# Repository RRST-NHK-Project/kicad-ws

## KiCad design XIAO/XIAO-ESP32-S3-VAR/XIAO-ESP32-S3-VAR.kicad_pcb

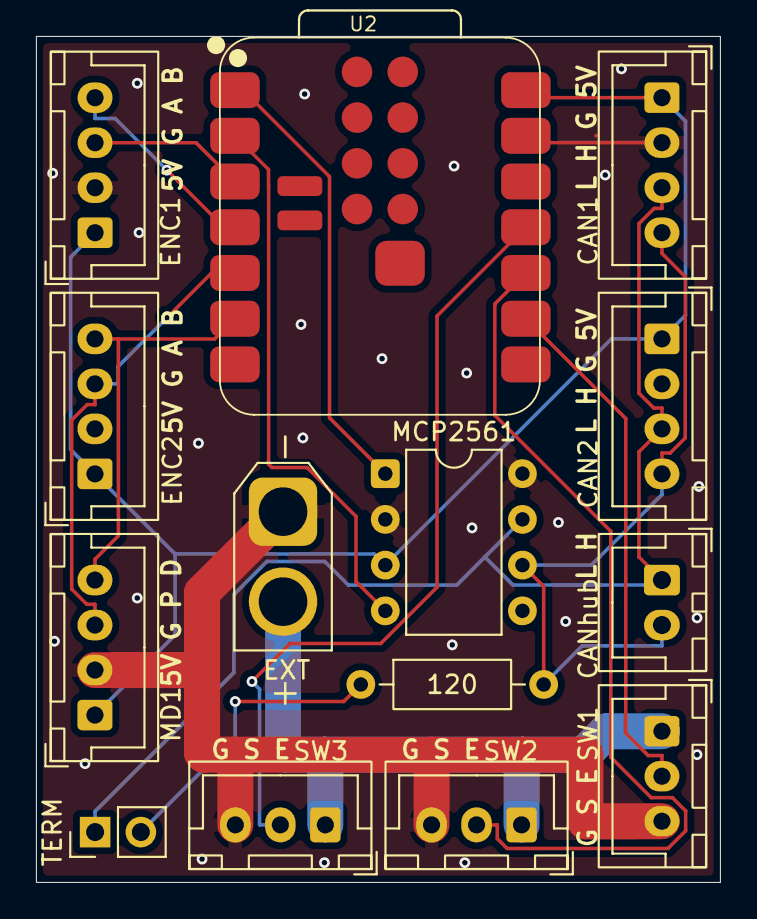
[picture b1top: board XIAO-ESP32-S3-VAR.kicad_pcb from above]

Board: 2 copper layers, 38.0 x 47.0 mm, 14 parts (0 on the bottom side), 15 nets.

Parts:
120: 120; R_Axial_DIN0207_L6.3mm_D2.5mm_P10.16mm_Horizontal
CAN1: CAN1; JST_XH_B4B-XH-A_1x04_P2.50mm_Vertical
CAN2: CAN2; JST_XH_B4B-XH-A_1x04_P2.50mm_Vertical
CANhub: CANhub; JST_XH_B2B-XH-A_1x02_P2.50mm_Vertical
ENC1: ENC1; JST_XH_B4B-XH-A_1x04_P2.50mm_Vertical
ENC2: ENC2; JST_XH_B4B-XH-A_1x04_P2.50mm_Vertical
EXT: Conn_01x02_Pin; AMASS_XT30U-M_1x02_P5.0mm_Vertical
MCP2561: DIP-8_W7.62mm
MD1: MD1; JST_XH_B4B-XH-A_1x04_P2.50mm_Vertical
SW1: SW1; JST_XH_B3B-XH-A_1x03_P2.50mm_Vertical
SW2: SW2; JST_XH_B3B-XH-A_1x03_P2.50mm_Vertical
SW3: SW3; JST_XH_B3B-XH-A_1x03_P2.50mm_Vertical
TERM: R120; PinHeader_1x02_P2.54mm_Vertical
U2: XIAO-ESP32-S3-SMD

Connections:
5V0: CAN1.1, CAN2.1, ENC1.1, ENC2.1, MCP2561.3 (Vdd), MD1.1, U2.14 (VBUS)
CANH: CAN1.3, CAN2.3, CANhub.1, MCP2561.7 (CANH), TERM.1
CANL: 120.2, CAN1.4, CAN2.4, CANhub.2, MCP2561.6 (CANL)
CAN_RX: MCP2561.4 (Rxd), U2.2 (GPIO2_A1_D1)
CAN_TX: MCP2561.1 (Txd), U2.1 (GPIO1_A0_D0)
ENC1_A/MD2P: ENC1.3, U2.3 (GPIO3_A2_D2)
ENC1_B/MD2D: ENC1.4, U2.4 (GPIO4_A3_D3)
EXT_POWER: EXT.2, SW1.1, SW2.1, SW3.1
GND: CAN1.2, CAN2.2, ENC1.2, ENC2.2, EXT.1, MCP2561.2 (Vss), MCP2561.8 (STBY), MD1.2, SW1.3, SW2.3, SW3.3, U2.13 (GND)
GPIO5: ENC2.3, MD1.3, U2.5 (GPIO5_A4_D4_SDA)
GPIO6: ENC2.4, MD1.4, U2.6 (GPIO6_A5_D5_SCL)
GPIO7: SW1.2, U2.9 (GPIO7_A8_D8_SCK)
GPIO8: SW2.2, U2.10 (GPIO8_A9_D9_MISO)
GPIO9: SW3.2, U2.11 (GPIO9_A10_D10_MOSI)
unnamed: 120.1, TERM.2

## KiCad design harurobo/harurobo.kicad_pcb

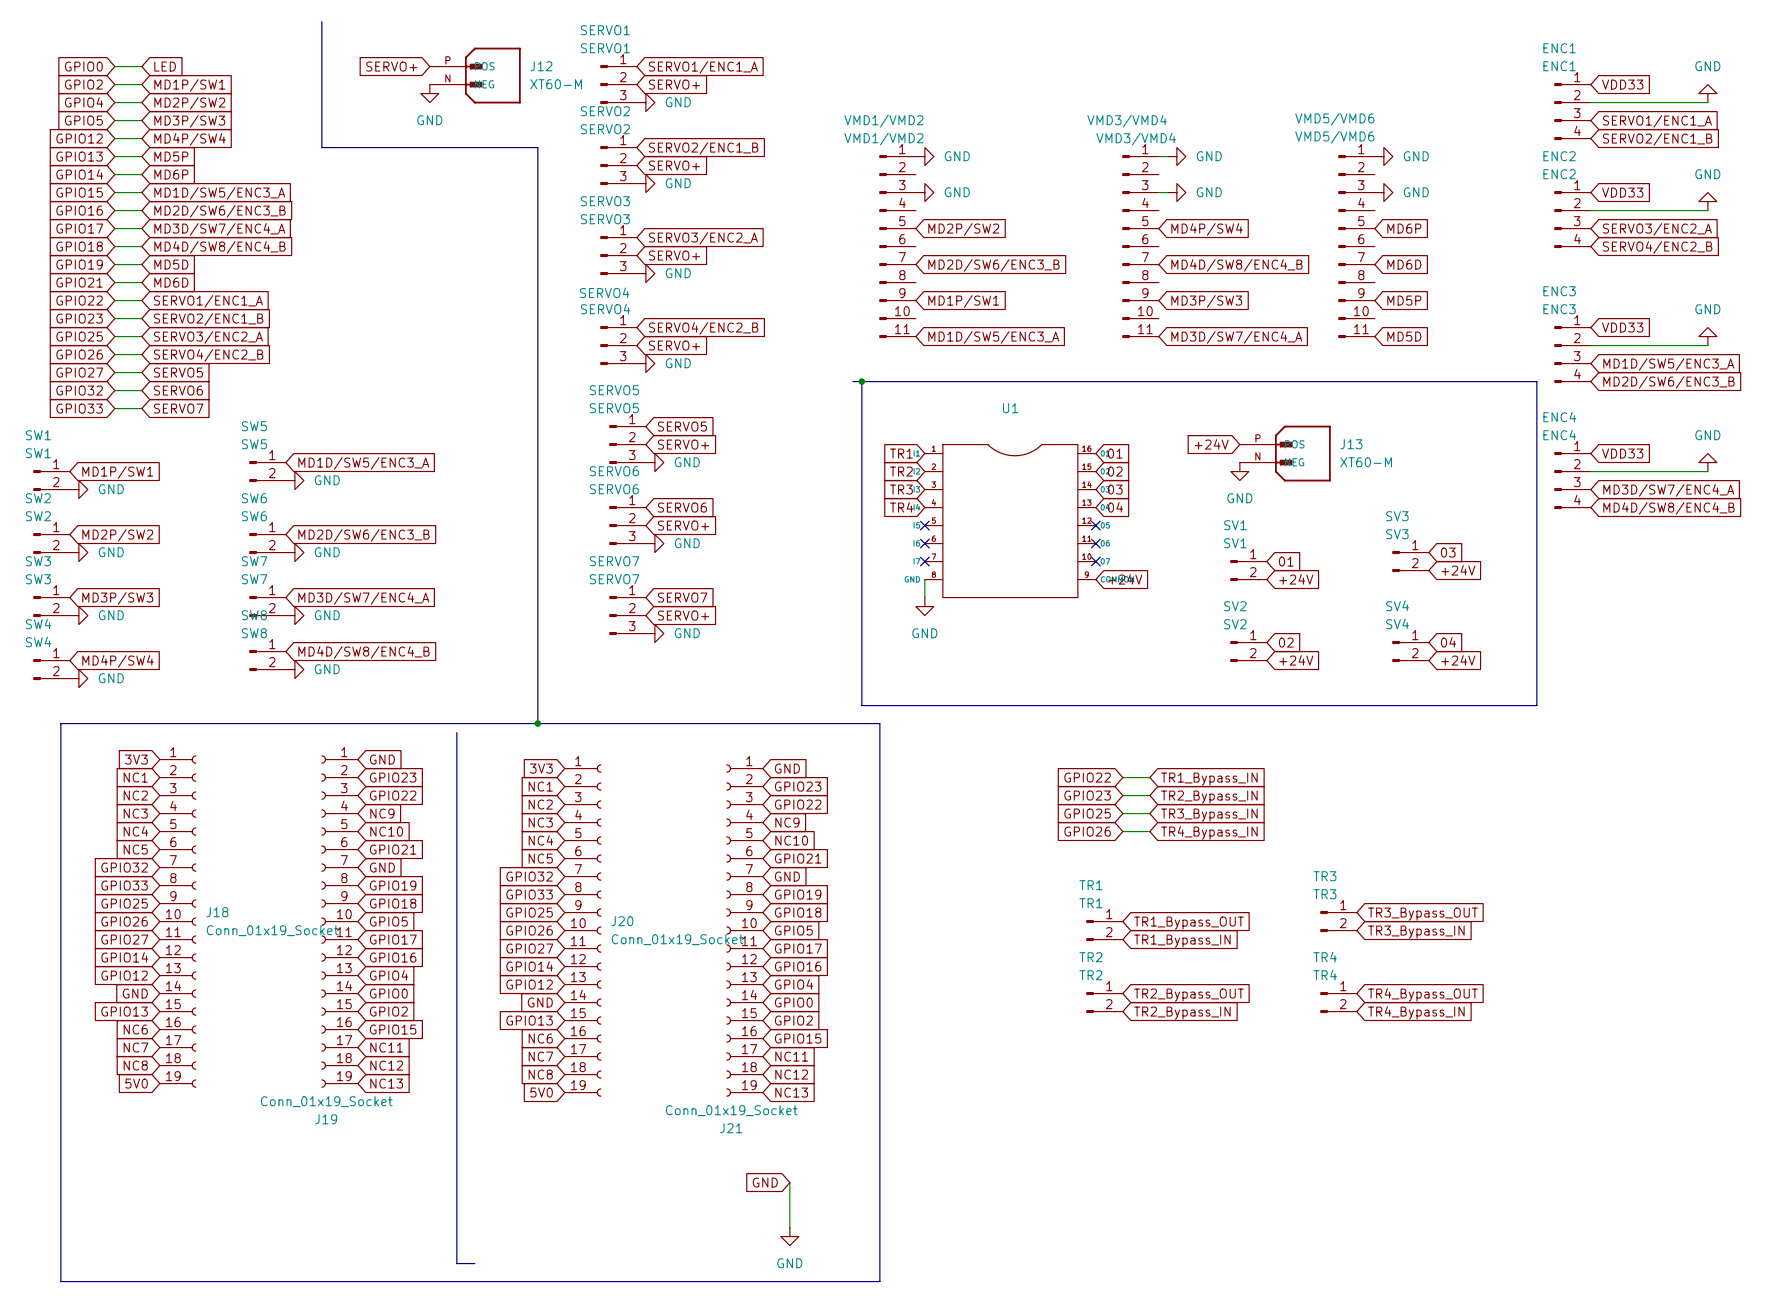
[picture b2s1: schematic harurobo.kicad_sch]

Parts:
ENC1: ENC1; JST_XH_B4B-XH-A_1x04_P2.50mm_Vertical
ENC2: ENC2; JST_XH_B4B-XH-A_1x04_P2.50mm_Vertical
ENC3: ENC3; JST_XH_B4B-XH-A_1x04_P2.50mm_Vertical
ENC4: ENC4; JST_XH_B4B-XH-A_1x04_P2.50mm_Vertical
J12, J13: XT60-M; AMASS_XT60-M; PARTREV V1.2
J18, J19, J20, J21: Conn_01x19_Socket; PinSocket_1x19_P2.54mm_Vertical
SERVO1: SERVO1; JST_XH_B3B-XH-A_1x03_P2.50mm_Vertical
SERVO2: SERVO2; JST_XH_B3B-XH-A_1x03_P2.50mm_Vertical
SERVO3: SERVO3; JST_XH_B3B-XH-A_1x03_P2.50mm_Vertical
SERVO4: SERVO4; JST_XH_B3B-XH-A_1x03_P2.50mm_Vertical
SERVO5: SERVO5; JST_XH_B3B-XH-A_1x03_P2.50mm_Vertical
SERVO6: SERVO6; JST_XH_B3B-XH-A_1x03_P2.50mm_Vertical
SERVO7: SERVO7; JST_XH_B3B-XH-A_1x03_P2.50mm_Vertical
SV1: SV1; JST_XH_B2B-XH-A_1x02_P2.50mm_Vertical
SV2: SV2; JST_XH_B2B-XH-A_1x02_P2.50mm_Vertical
SV3: SV3; JST_XH_B2B-XH-A_1x02_P2.50mm_Vertical
SV4: SV4; JST_XH_B2B-XH-A_1x02_P2.50mm_Vertical
SW1: SW1; JST_XH_B2B-XH-A_1x02_P2.50mm_Vertical
SW2: SW2; JST_XH_B2B-XH-A_1x02_P2.50mm_Vertical
SW3: SW3; JST_XH_B2B-XH-A_1x02_P2.50mm_Vertical
SW4: SW4; JST_XH_B2B-XH-A_1x02_P2.50mm_Vertical
SW5: SW5; JST_XH_B2B-XH-A_1x02_P2.50mm_Vertical
SW6: SW6; JST_XH_B2B-XH-A_1x02_P2.50mm_Vertical
SW7: SW7; JST_XH_B2B-XH-A_1x02_P2.50mm_Vertical
SW8: SW8; JST_XH_B2B-XH-A_1x02_P2.50mm_Vertical
TR1: TR1; PinHeader_1x02_P2.54mm_Vertical
TR2: TR2; PinHeader_1x02_P2.54mm_Vertical
TR3: TR3; PinHeader_1x02_P2.54mm_Vertical
TR4: TR4; PinHeader_1x02_P2.54mm_Vertical
U1: DIP-16_W7.62mm
VMD1/VMD2: VMD1/VMD2; PinHeader_1x11_P2.54mm_Vertical
VMD3/VMD4: VMD3/VMD4; PinHeader_1x11_P2.54mm_Vertical
VMD5/VMD6: VMD5/VMD6; PinHeader_1x11_P2.54mm_Vertical

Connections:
01: SV1.1
02: SV2.1
03: SV3.1
3V3: J18.1, J20.1
04: SV4.1
5V0: J18.19, J20.19
+24V: J13.P (POS), SV1.2, SV2.2, SV3.2, SV4.2
GND: ENC1.2, ENC2.2, ENC3.2, ENC4.2, J12.N (NEG), J13.N (NEG), J18.14, J19.1, J19.7, J20.14, J21.1, J21.7, SERVO1.3, SERVO2.3, SERVO3.3, SERVO4.3, SERVO5.3, SERVO6.3, SERVO7.3, SW1.2, SW2.2, SW3.2, SW4.2, SW5.2, SW6.2, SW7.2, SW8.2, VMD1/VMD2.1, VMD1/VMD2.3, VMD3/VMD4.1, VMD3/VMD4.3, VMD5/VMD6.1, VMD5/VMD6.3
GPIO0: J19.14, J21.14
GPIO2: J19.15, J21.15, SW1.1, VMD1/VMD2.9
GPIO4: J19.13, J21.13, SW2.1, VMD1/VMD2.5
GPIO5: J19.10, J21.10, SW3.1, VMD3/VMD4.9
GPIO12: J18.13, J20.13, SW4.1, VMD3/VMD4.5
GPIO13: J18.15, J20.15, VMD5/VMD6.9
GPIO14: J18.12, J20.12, VMD5/VMD6.5
GPIO15: ENC3.3, J19.16, J21.16, SW5.1, VMD1/VMD2.11
GPIO16: ENC3.4, J19.12, J21.12, SW6.1, VMD1/VMD2.7
GPIO17: ENC4.3, J19.11, J21.11, SW7.1, VMD3/VMD4.11
GPIO18: ENC4.4, J19.9, J21.9, SW8.1, VMD3/VMD4.7
GPIO19: J19.8, J21.8, VMD5/VMD6.11
GPIO21: J19.6, J21.6, VMD5/VMD6.7
GPIO22: ENC1.3, J19.3, J21.3, SERVO1.1, TR1.2
GPIO23: ENC1.4, J19.2, J21.2, SERVO2.1, TR2.2
GPIO25: ENC2.3, J18.9, J20.9, SERVO3.1, TR3.2
GPIO26: ENC2.4, J18.10, J20.10, SERVO4.1, TR4.2
GPIO27: J18.11, J20.11, SERVO5.1
GPIO32: J18.7, J20.7, SERVO6.1
GPIO33: J18.8, J20.8, SERVO7.1
NC1: J18.2, J20.2
NC2: J18.3, J20.3
NC3: J18.4, J20.4
NC4: J18.5, J20.5
NC5: J18.6, J20.6
NC6: J18.16, J20.16
NC7: J18.17, J20.17
NC8: J18.18, J20.18
NC9: J19.4, J21.4
NC10: J19.5, J21.5
NC11: J19.17, J21.17
NC12: J19.18, J21.18
NC13: J19.19, J21.19
SERVO+: J12.P (POS), SERVO1.2, SERVO2.2, SERVO3.2, SERVO4.2, SERVO5.2, SERVO6.2, SERVO7.2
TR1_Bypass_OUT: TR1.1
TR2_Bypass_OUT: TR2.1
TR3_Bypass_OUT: TR3.1
TR4_Bypass_OUT: TR4.1
VDD33: ENC1.1, ENC2.1, ENC3.1, ENC4.1

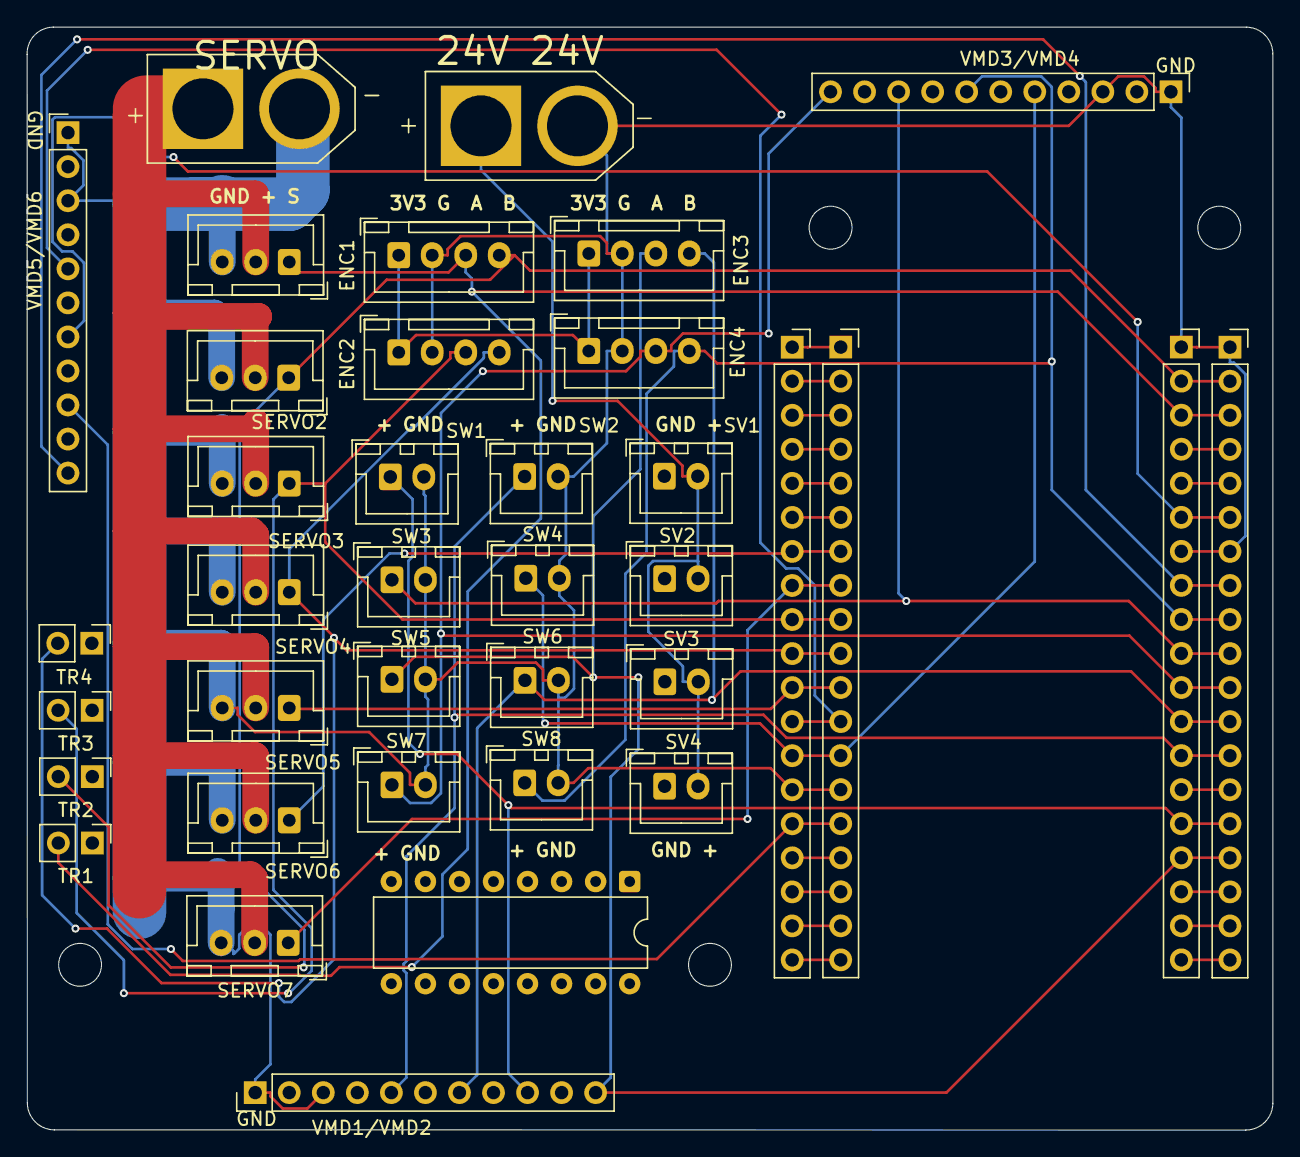
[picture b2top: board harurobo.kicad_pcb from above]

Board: 2 copper layers, 93.0 x 82.3 mm, 41 parts (0 on the bottom side), 39 nets.

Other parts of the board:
REF1**, REF2**, REF3**, REF4**: MountingHole_3.2mm_M3

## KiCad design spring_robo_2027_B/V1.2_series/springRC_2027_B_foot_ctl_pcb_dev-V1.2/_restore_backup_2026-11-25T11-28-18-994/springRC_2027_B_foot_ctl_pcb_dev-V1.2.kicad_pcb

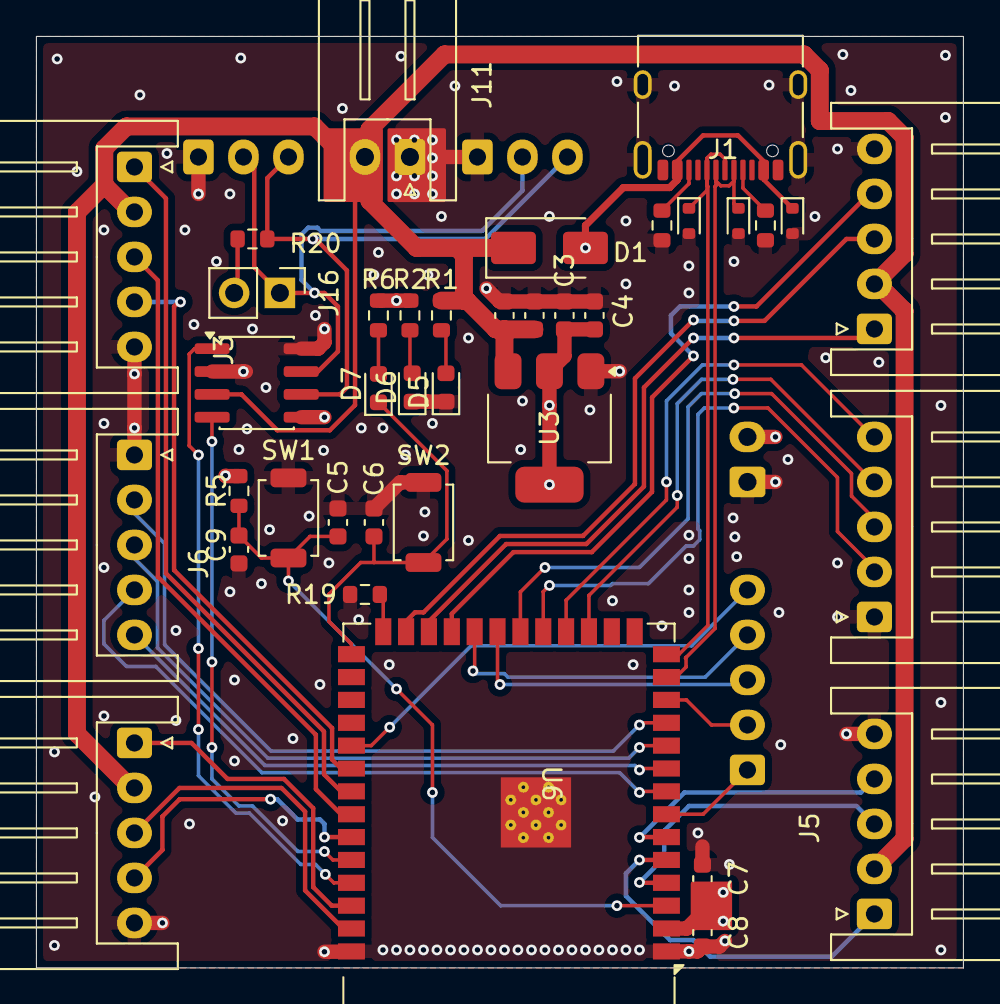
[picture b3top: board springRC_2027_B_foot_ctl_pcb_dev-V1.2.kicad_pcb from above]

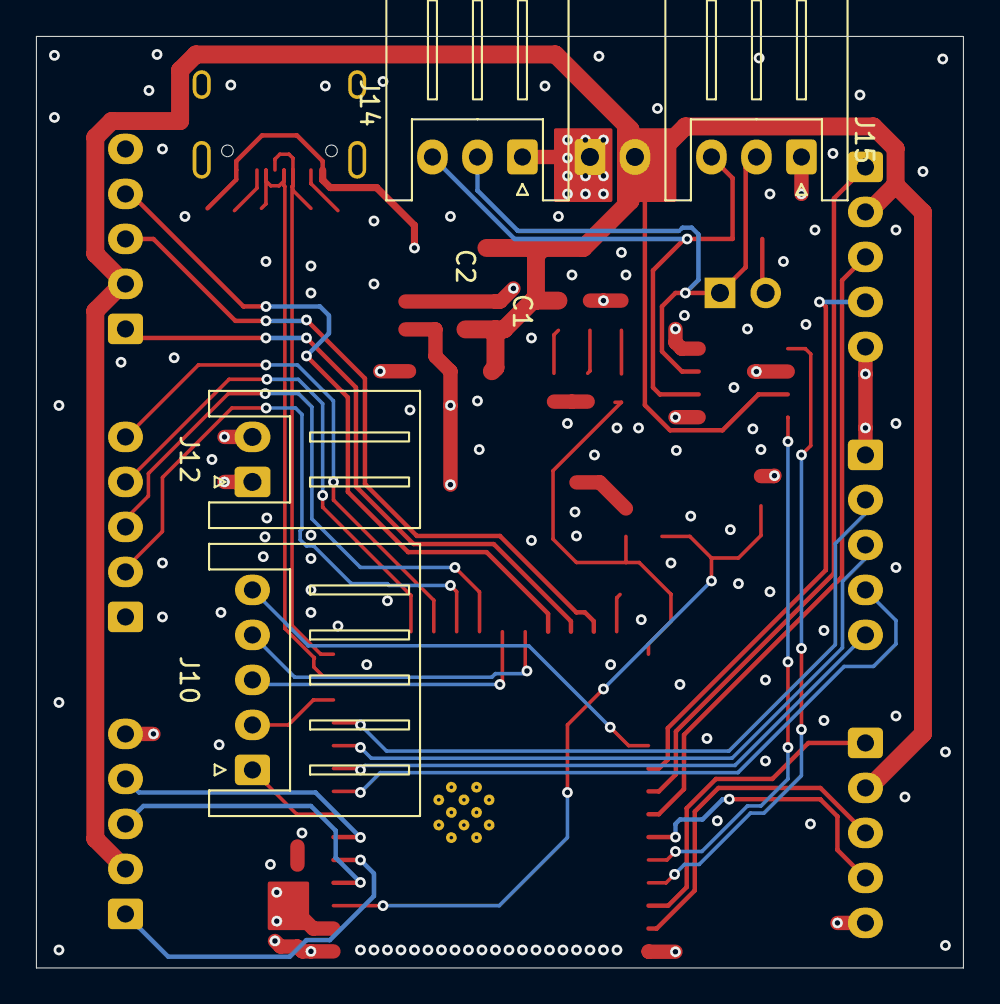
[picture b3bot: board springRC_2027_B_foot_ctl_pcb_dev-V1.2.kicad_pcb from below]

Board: 4 copper layers, 51.5 x 51.8 mm, 42 parts (4 on the bottom side), 44 nets.

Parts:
C1, C3, C7: 10uF; C_0603_1608Metric
C2, C4, C5, C6, C8: 100nF; C_0603_1608Metric
C9: 1uF; C_0603_1608Metric
D1: SS14; D_SMA
D2, D3, D4: LESD5D5.0CT1G; D_SOD-523
D5, D6, D7: LED; LED_0603_1608Metric
J1: USB_C_Receptacle_USB2.0_16P; USB_C_Receptacle_XKB_U262-16XN-4BVC11
J2, J3, J4, J5, J6, J7, J10: Conn_01x05_Socket; JST_XH_S5B-XH-A_1x05_P2.50mm_Horizontal
J11, J12: Conn_01x02_Socket; JST_XH_S2B-XH-A_1x02_P2.50mm_Horizontal
J14, J15: Conn_01x03_Socket; JST_XH_S3B-XH-A_1x03_P2.50mm_Horizontal
J16: Conn_01x02_Pin; PinHeader_1x02_P2.54mm_Vertical
R1, R2, R3, R4: 5.1k; R_0603_1608Metric
R5: 10k; R_0603_1608Metric
R6: 330; R_0603_1608Metric
R19: 1k; R_0603_1608Metric
R20: 120; R_0603_1608Metric
SW1, SW2: SW_Push; SW_SPST_TS-1088-xR020
U1: MCP2562FD-E-SN; SOIC-8_3.9x4.9mm_P1.27mm
U3: LD1117S33TR_SOT223; SOT-223-3_TabPin2
U6: ESP32-S3-WROOM-1-N16R8; ESP32-S3-WROOM-1

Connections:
3V3: C3.2, C4.2, C7.1, C8.1, J12.2, R2.1, R5.1, R6.2, U1.5 (Vio), U3.2 (VO), U6.2 (3V3)
+5V: C1.1, C2.1, D1.1 (K), J2.2, J3.2, J4.2, J5.2, J11.2, R1.1, U1.3 (VDD), U3.3 (VI)
CAN_H: J14.2, J15.2, J16.1, U1.7 (CANH)
CAN_L: J14.3, J15.3, R20.1, U1.6 (CANL)
CAN_RX: U1.4 (RXD), U6.36 (RXD0)
CAN_TX: U1.1 (TXD), U6.37 (TXD0)
DN: D3.1, J1.A7 (D-), J1.B7 (D-), U6.13 (USB_D-)
DP: D4.1, J1.A6 (D+), J1.B6 (D+), U6.14 (USB_D+)
EN: C5.1, C9.1, R5.2, SW1.2, U6.3 (EN)
ENC1_A: J2.3, U6.39 (IO1)
ENC1_B: J2.1, U6.38 (IO2)
ENC1_X: J2.4, U6.35 (IO42)
ENC2_A: J3.3, U6.34 (IO41)
ENC2_B: J3.1, U6.33 (IO40)
ENC2_X: J3.4, U6.32 (IO39)
ENC3_A: J4.3, U6.25 (IO48)
ENC3_B: J4.1, U6.24 (IO47)
ENC3_X: J4.4, U6.23 (IO21)
ENC4_A: J5.3, U6.4 (IO4)
ENC4_B: J5.1, U6.5 (IO5)
ENC4_X: J5.4, U6.6 (IO6)
GND: C1.2, C2.2, C3.1, C4.1, C5.2, C6.2, C7.2, C8.2, C9.2, D2.2, D3.2, D4.2, D5.1 (K), D6.1 (K), J1.A1 (GND), J1.A12 (GND), J1.B1 (GND), J1.B12 (GND), J1.S1 (SHIELD), J2.5, J3.5, J4.5, J5.5, J6.1, J7.1, J11.1, J12.1, J14.1, J15.1, R3.2, R4.2, R19.2, SW1.1, SW2.1, U1.2 (VSS), U1.8 (STBY), U3.1 (GND), U6.1 (GND), U6.40 (GND), U6.41 (GND)
IO0: C6.1, D7.1 (K), SW2.2, U6.27 (IO0)
IO7: J10.1, U6.7 (IO7)
IO8: J10.2, U6.12 (IO8)
IO9: J7.4, U6.17 (IO9)
IO10: J7.5, U6.18 (IO10)
IO11: J7.2, U6.19 (IO11)
IO12: J7.3, U6.20 (IO12)
IO13: J10.3, U6.21 (IO13)
IO14: J10.4, U6.22 (IO14)
IO15: J6.4, U6.8 (IO15)
IO16: J6.5, U6.9 (IO16)
IO17: J6.3, U6.10 (IO17)
IO18: J6.2, U6.11 (IO18)
IO38: J10.5, U6.31 (IO38)
IO45: R19.1, U6.26 (IO45)
unnamed: D5.2 (A), R1.2
unnamed: D6.2 (A), R2.2
unnamed: D7.2 (A), R6.1
unnamed: J1.A5 (CC1), R4.1
unnamed: J1.B5 (CC2), R3.1
unnamed: J16.2, R20.2
VBUS: D1.2 (A), D2.1, J1.A4 (VBUS), J1.A9 (VBUS), J1.B4 (VBUS), J1.B9 (VBUS)

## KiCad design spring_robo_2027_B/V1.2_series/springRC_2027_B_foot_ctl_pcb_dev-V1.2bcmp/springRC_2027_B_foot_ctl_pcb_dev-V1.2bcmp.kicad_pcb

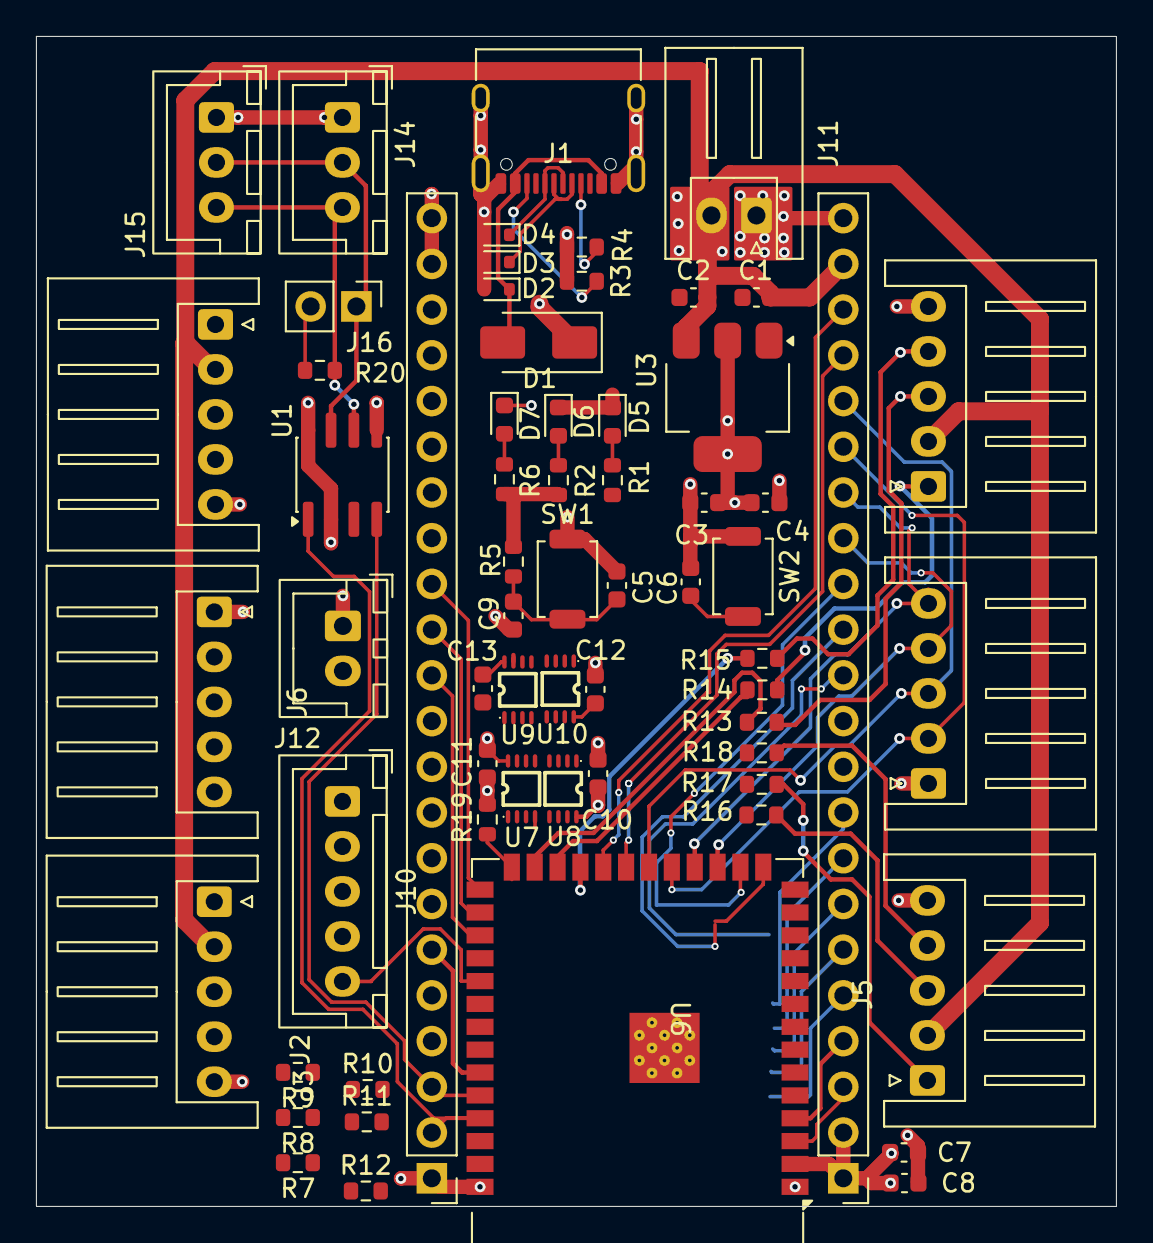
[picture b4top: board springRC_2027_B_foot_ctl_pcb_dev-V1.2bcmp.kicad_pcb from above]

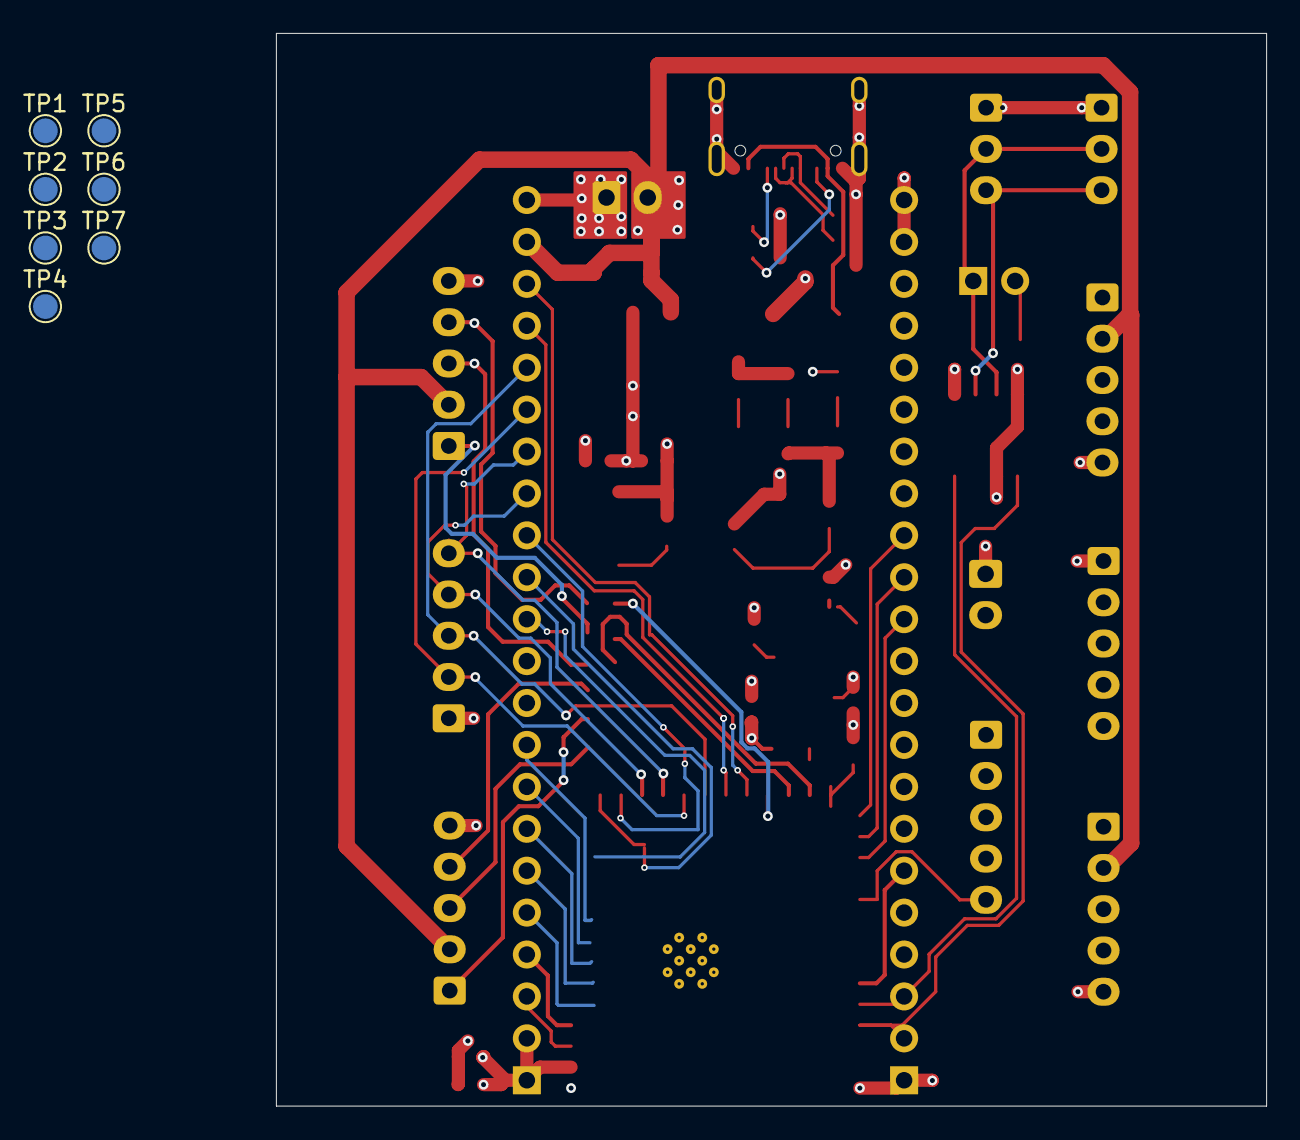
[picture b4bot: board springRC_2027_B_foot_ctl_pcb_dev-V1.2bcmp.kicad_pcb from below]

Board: 4 copper layers, 60.0 x 65.0 mm, 71 parts (7 on the bottom side), 61 nets.

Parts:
C1, C3, C7: 10uF; C_0603_1608Metric
C2, C4, C5, C6, C8, C10, C11, C12, C13: 100nF; C_0603_1608Metric
C9: 1uF; C_0603_1608Metric
D1: SS14; D_SMA
D2, D3, D4: LESD5D5.0CT1G; D_SOD-523
D5, D6, D7: LED; LED_0603_1608Metric
J1: USB_C_Receptacle_USB2.0_16P; USB_C_Receptacle_XKB_U262-16XN-4BVC11
J2, J3, J4, J5, J6, J7: Conn_01x05_Socket; JST_XH_S5B-XH-A_1x05_P2.50mm_Horizontal
J8, J9: Conn_01x22_Pin; PinHeader_1x22_P2.54mm_Vertical
J10: Conn_01x05_Socket; JST_XH_B5B-XH-A_1x05_P2.50mm_Vertical
J11: Conn_01x02_Socket; JST_XH_S2B-XH-A_1x02_P2.50mm_Horizontal
J12: Conn_01x02_Socket; JST_XH_B2B-XH-A_1x02_P2.50mm_Vertical
J14, J15: Conn_01x03_Socket; JST_XH_B3B-XH-A_1x03_P2.50mm_Vertical
J16: Conn_01x02_Pin; PinHeader_1x02_P2.54mm_Vertical
R1, R2, R3, R4: 5.1k; R_0603_1608Metric
R5: 10k; R_0603_1608Metric
R6: 330; R_0603_1608Metric
R7, R8, R9, R10, R11, R12, R13, R14, R15, R16, R17, R18: 0R; R_0603_1608Metric
R19: 1k; R_0603_1608Metric
R20: 120; R_0603_1608Metric
SW1, SW2: SW_Push; SW_SPST_TS-1088-xR020
TP1: VBUS; TestPoint_Pad_D1.5mm
TP2: CAN_H; TestPoint_Pad_D1.5mm
TP3: CAN_L; TestPoint_Pad_D1.5mm
TP4, TP7: GND; TestPoint_Pad_D1.5mm
TP5: DP; TestPoint_Pad_D1.5mm
TP6: DN; TestPoint_Pad_D1.5mm
U1: MCP2562FD-E-SN; SOIC-8_3.9x4.9mm_P1.27mm
U3: LD1117S33TR_SOT223; SOT-223-3_TabPin2
U6: ESP32-S3-WROOM-1-N16R8; ESP32-S3-WROOM-1
U7, U8, U9, U10: SN74LVC3G17DCUR; VSSOP-8_L2.1-W2.4-P0.50-LS3.2-BR

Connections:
3V3: C3.2, C4.2, C7.1, C8.1, C10.1, C11.1, C12.1, C13.1, J8.1, J8.2, J12.2, R2.1, R5.1, R6.2, U1.5 (Vio), U3.2 (VO), U6.2 (3V3), U7.8 (VCC), U8.8 (VCC), U9.8 (VCC), U10.8 (VCC)
+5V: C1.1, C2.1, D1.1 (K), J2.2, J3.2, J4.2, J5.2, J8.21, J11.2, R1.1, U1.3 (VDD), U3.3 (VI)
CAN_H: J14.2, J15.2, J16.1, TP2.1 (1_1), U1.7 (CANH)
CAN_L: J14.3, J15.3, R20.1, TP3.1 (1_1), U1.6 (CANL)
CAN_RX: J9.3, U1.4 (RXD), U6.36 (RXD0)
CAN_TX: J9.2, U1.1 (TXD), U6.37 (TXD0)
DN: D3.1, J1.A7 (D-), J1.B7 (D-), J9.20, TP6.1 (1_1), U6.13 (USB_D-)
DP: D4.1, J1.A6 (D+), J1.B6 (D+), J9.19, TP5.1 (1_1), U6.14 (USB_D+)
EN: C5.1, C9.1, J8.3, R5.2, SW1.2, U6.3 (EN)
ENC1_A: J2.3, R7.1, U7.1 (1A)
ENC1_A_BUF: J9.4, R7.2, U6.39 (IO1), U7.7 (1Y)
ENC1_B: J2.1, R8.1, U7.3 (2A)
ENC1_B_BUF: J9.5, R8.2, U6.38 (IO2), U7.5 (2Y)
ENC1_X: J2.4, R9.1, U7.6 (3A)
ENC1_X_BUF: J9.6, R9.2, U6.35 (IO42), U7.2 (3Y)
ENC2_A: J3.3, R10.1, U8.1 (1A)
ENC2_A_BUF: J9.7, R10.2, U6.34 (IO41), U8.7 (1Y)
ENC2_B: J3.1, R11.1, U8.3 (2A)
ENC2_B_BUF: J9.8, R11.2, U6.33 (IO40), U8.5 (2Y)
ENC2_X: J3.4, R12.1, U8.6 (3A)
ENC2_X_BUF: J9.9, R12.2, U6.32 (IO39), U8.2 (3Y)
ENC3_A: J4.3, R13.1, U9.1 (1A)
ENC3_A_BUF: J9.16, R13.2, U6.25 (IO48), U9.7 (1Y)
ENC3_B: J4.1, R14.1, U9.3 (2A)
ENC3_B_BUF: J9.17, R14.2, U6.24 (IO47), U9.5 (2Y)
ENC3_X: J4.4, R15.1, U9.6 (3A)
ENC3_X_BUF: J9.18, R15.2, U6.23 (IO21), U9.2 (3Y)
ENC4_A: J5.3, R16.1, U10.1 (1A)
ENC4_A_BUF: J8.4, R16.2, U6.4 (IO4), U10.7 (1Y)
ENC4_B: J5.1, R17.1, U10.3 (2A)
ENC4_B_BUF: J8.5, R17.2, U6.5 (IO5), U10.5 (2Y)
ENC4_X: J5.4, R18.1, U10.6 (3A)
ENC4_X_BUF: J8.6, R18.2, U6.6 (IO6), U10.2 (3Y)
GND: C1.2, C2.2, C3.1, C4.1, C5.2, C6.2, C7.2, C8.2, C9.2, C10.2, C11.2, C12.2, C13.2, D2.2, D3.2, D4.2, D5.1 (K), D6.1 (K), J1.A1 (GND), J1.A12 (GND), J1.B1 (GND), J1.B12 (GND), J1.S1 (SHIELD), J2.5, J3.5, J4.5, J5.5, J6.1, J7.1, J8.22, J9.1, J9.21, J9.22, J11.1, J12.1, J14.1, J15.1, R3.2, R4.2, R19.2, SW1.1, SW2.1, TP4.1 (1_1), TP7.1 (1_1), U1.2 (VSS), U1.8 (STBY), U3.1 (GND), U6.1 (GND), U6.40 (GND), U6.41 (GND), U7.4 (GND), U8.4 (GND), U9.4 (GND), U10.4 (GND)
IO0: C6.1, D7.1 (K), J9.14, SW2.2, U6.27 (IO0)
IO3: J8.13, U6.15 (IO3)
IO7: J8.7, J10.1, U6.7 (IO7)
IO8: J8.12, J10.2, U6.12 (IO8)
IO9: J7.4, J8.15, U6.17 (IO9)
IO10: J7.5, J8.16, U6.18 (IO10)
IO11: J7.2, J8.17, U6.19 (IO11)
IO12: J7.3, J8.18, U6.20 (IO12)
IO13: J8.19, J10.3, U6.21 (IO13)
IO14: J8.20, J10.4, U6.22 (IO14)
IO15: J6.4, J8.8, U6.8 (IO15)
IO16: J6.5, J8.9, U6.9 (IO16)
IO17: J6.3, J8.10, U6.10 (IO17)
IO18: J6.2, J8.11, U6.11 (IO18)
IO35: J9.13, U6.28 (IO35)
IO36: J9.12, U6.29 (IO36)
IO37: J9.11, U6.30 (IO37)
IO38: J9.10, J10.5, U6.31 (IO38)
IO45: J9.15, R19.1, U6.26 (IO45)
IO46: J8.14, U6.16 (IO46)
unnamed: D5.2 (A), R1.2
unnamed: D6.2 (A), R2.2
unnamed: D7.2 (A), R6.1
unnamed: J1.A5 (CC1), R4.1
unnamed: J1.B5 (CC2), R3.1
unnamed: J16.2, R20.2
VBUS: D1.2 (A), D2.1, J1.A4 (VBUS), J1.A9 (VBUS), J1.B4 (VBUS), J1.B9 (VBUS), TP1.1 (1_1)

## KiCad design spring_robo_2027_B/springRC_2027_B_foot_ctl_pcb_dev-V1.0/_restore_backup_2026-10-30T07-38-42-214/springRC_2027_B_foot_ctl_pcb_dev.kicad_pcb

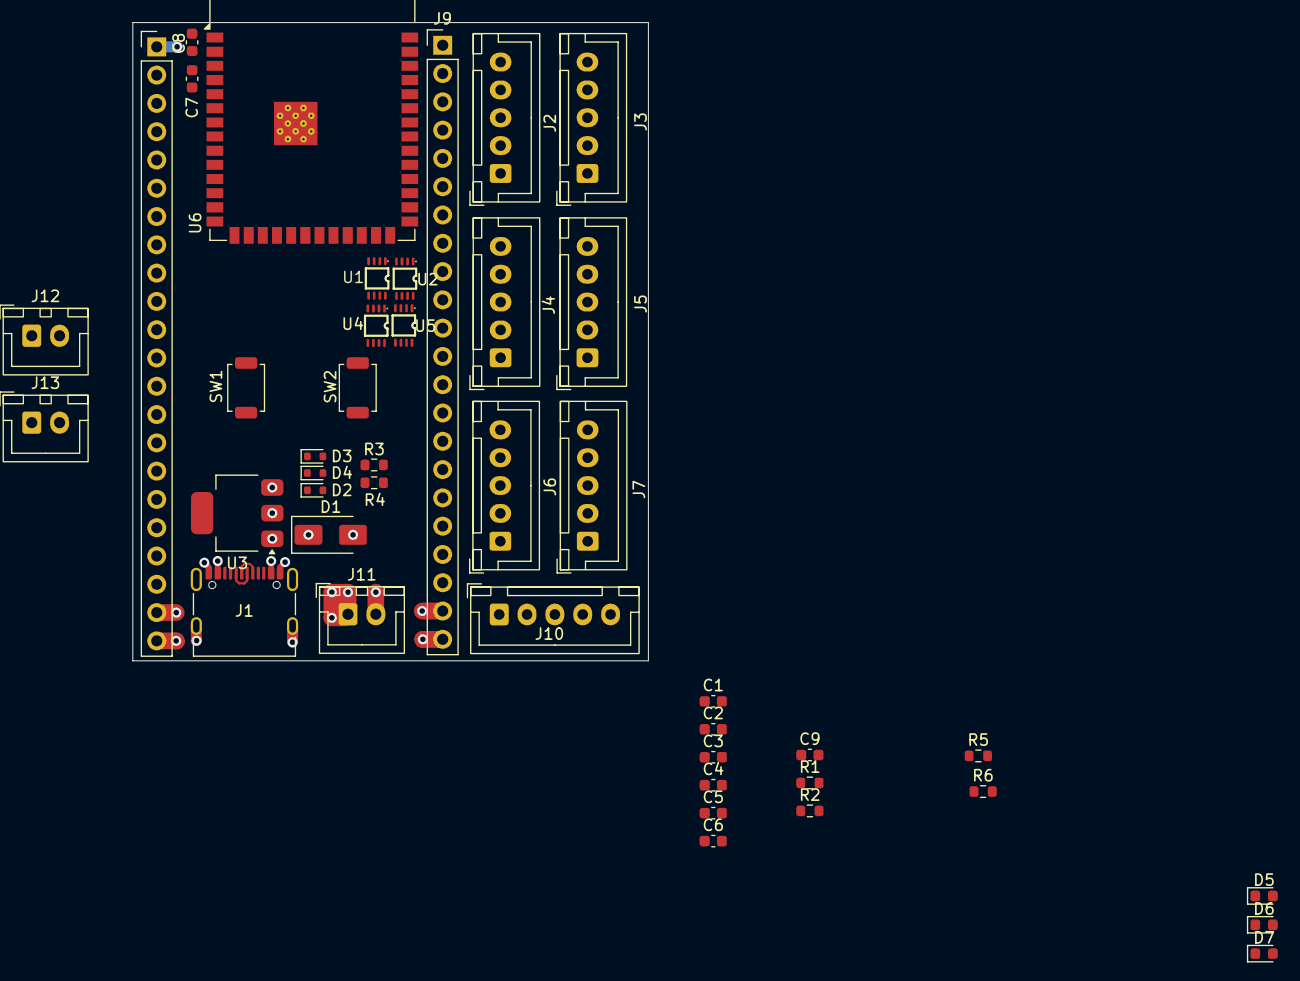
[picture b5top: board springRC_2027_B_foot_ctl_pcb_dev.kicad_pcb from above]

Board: 4 copper layers, 46.3 x 57.3 mm, 43 parts (0 on the bottom side), 58 nets.

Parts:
C1, C4, C7: 10uF; C_0603_1608Metric
C2, C3, C5, C6, C8: 100nF; C_0603_1608Metric
C9: 1uF; C_0603_1608Metric
D1: SS14; D_SMA
D2, D3, D4: LESD5D5.0CT1G; D_SOD-523
D5, D6, D7: LED; LED_0603_1608Metric
J1: USB_C_Receptacle_USB2.0_16P; USB_C_Receptacle_XKB_U262-16XN-4BVC11
J2, J3, J4, J5, J6, J7, J10: Conn_01x05_Socket; JST_XH_B5B-XH-A_1x05_P2.50mm_Vertical
J8, J9: Conn_01x22_Pin; PinHeader_1x22_P2.54mm_Vertical
J11, J12, J13: Conn_01x02_Socket; JST_XH_B2B-XH-A_1x02_P2.50mm_Vertical
R1, R2: 5.1k; R_0603_1608Metric
R3, R4: 5.1K; R_0603_1608Metric
R5: 10k; R_0603_1608Metric
R6: 330; R_0603_1608Metric
SW1, SW2: SW_Push; SW_SPST_TS-1088-xR020
U1, U2, U4, U5: SN74LVC3G17DCUR; VSSOP-8_L2.1-W2.4-P0.50-LS3.2-BR
U3: LD1117S33TR_SOT223; SOT-223-3_TabPin2
U6: ESP32-S3-WROOM-1

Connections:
3V3: C3.1, C4.1, C7.1, C8.1, D7.2 (A), J8.1, J8.2, J12.2, J13.2, R2.1, R5.1, U1.8 (VCC), U2.8 (VCC), U3.2 (VO), U4.8 (VCC), U5.8 (VCC), U6.2 (3V3)
+5V: C1.1, C2.1, D1.1 (K), J2.2, J3.2, J4.2, J5.2, J8.21, J11.2, R1.1, U3.3 (VI)
DN: D3.1, J1.A7 (D-), J1.B7 (D-), J9.20, U6.13 (USB_D-)
DP: D4.1, J1.A6 (D+), J1.B6 (D+), J9.19, U6.14 (USB_D+)
EN: C5.1, C9.1, J8.3, R5.2, SW1.2, U6.3 (EN)
ENC1_A: J2.3, U1.1 (1A)
ENC1_A_BUF: J9.4, U1.7 (1Y), U6.39 (IO1)
ENC1_B: J2.1, U1.3 (2A)
ENC1_B_BUF: J9.5, U1.5 (2Y), U6.38 (IO2)
ENC1_X: J2.4, U1.6 (3A)
ENC1_X_BUF: J9.6, U1.2 (3Y), U6.35 (IO42)
ENC2_A: J3.3, U2.1 (1A)
ENC2_A_BUF: J9.7, U2.7 (1Y), U6.34 (IO41)
ENC2_B: J3.1, U2.3 (2A)
ENC2_B_BUF: J9.8, U2.5 (2Y), U6.33 (IO40)
ENC2_X: J3.4, U2.6 (3A)
ENC2_X_BUF: J9.9, U2.2 (3Y), U6.32 (IO39)
ENC3_A: J4.3, U4.1 (1A)
ENC3_A_BUF: J9.16, U4.7 (1Y), U6.25 (IO48)
ENC3_B: J4.1, U4.3 (2A)
ENC3_B_BUF: J9.17, U4.5 (2Y), U6.24 (IO47)
ENC3_X: J4.4, U4.6 (3A)
ENC3_X_BUF: J9.18, U4.2 (3Y), U6.23 (IO21)
ENC4_A: J5.3, U5.1 (1A)
ENC4_A_BUF: J8.4, U5.7 (1Y), U6.4 (IO4)
ENC4_B: J5.1, U5.3 (2A)
ENC4_B_BUF: J8.5, U5.5 (2Y), U6.5 (IO5)
ENC4_X: J5.4, U5.6 (3A)
ENC4_X_BUF: J8.6, U5.2 (3Y), U6.6 (IO6)
GND: C1.2, C2.2, C3.2, C4.2, C5.2, C6.2, C7.2, C8.2, C9.2, D2.2, D3.2, D4.2, D5.1 (K), D6.1 (K), J1.A1 (GND), J1.A12 (GND), J1.B1 (GND), J1.B12 (GND), J2.5, J3.5, J4.5, J5.5, J6.1, J7.1, J8.22, J9.1, J9.21, J9.22, J11.1, J12.1, J13.1, R3.2, R4.2, SW1.1, SW2.1, U1.4 (GND), U2.4 (GND), U3.1 (GND), U4.4 (GND), U5.4 (GND), U6.1 (GND), U6.40 (GND), U6.41 (GND)
IO0: C6.1, J9.14, R6.2, SW2.2, U6.27 (IO0)
IO3: J8.13, U6.15 (IO3)
IO7: J8.7, J10.1, U6.7 (IO7)
IO8: J8.12, J10.2, U6.12 (IO8)
IO9: J7.4, J8.15, U6.17 (IO9)
IO10: J7.5, J8.16, U6.18 (IO10)
IO11: J7.2, J8.17, U6.19 (IO11)
IO12: J7.3, J8.18, U6.20 (IO12)
IO13: J8.19, J10.3, U6.21 (IO13)
IO14: J8.20, J10.4, U6.22 (IO14)
IO15: J6.4, J8.8, U6.8 (IO15)
IO16: J6.5, J8.9, U6.9 (IO16)
IO17: J6.3, J8.10, U6.10 (IO17)
IO18: J6.2, J8.11, U6.11 (IO18)
IO35: J9.13, U6.28 (IO35)
IO36: J9.12, U6.29 (IO36)
IO37: J9.11, U6.30 (IO37)
IO38: J9.10, J10.5, U6.31 (IO38)
IO45: J9.15, U6.26 (IO45)
IO46: J8.14, U6.16 (IO46)
unnamed: D5.2 (A), R1.2
unnamed: D6.2 (A), R2.2
unnamed: D7.1 (K), R6.1
unnamed: J1.A5 (CC1), R4.1
unnamed: J1.B5 (CC2), R3.1
RXD0: J9.3, U6.36 (RXD0)
TXD0: J9.2, U6.37 (TXD0)
VBUS: D1.2 (A), D2.1, J1.A4 (VBUS), J1.A9 (VBUS), J1.B4 (VBUS), J1.B9 (VBUS)
